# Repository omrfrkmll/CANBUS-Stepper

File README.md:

# ⚡ CANBUS-Stepper

<p align="center">
  <b>ESP32-S3 Based Closed-Loop Smart CAN Bus Stepper Motor Driver Board (v1.1)</b>
</p>

<p align="center">

</p>

<p align="center">
  <a href="#-overview">Overview</a> •
  <a href="#-development-status">Development Status</a> •
  <a href="#-hardware-features--specifications">Hardware Specs</a> •
  <a href="#-pcb--hardware-preview">PCB Preview</a> •
  <a href="#-schematics--mechanical-cad">Schematic & CAD</a> •
  <a href="#-firmware--control-sdk">Firmware & SDK</a> •
  <a href="#-official-hardware--custom-engineering">Official Hardware & Services</a> •
  <a href="#-license">License</a>
</p>

---

## 📌 Overview

**CANBUS-Stepper** is a high-performance smart stepper motor driver board powered by the **ESP32-S3** dual-core microcontroller. Designed specifically for 3D printer toolheads, robotic actuators, AGVs, CNC axes, and industrial automation, this board integrates:

- **Ultra-Quiet Motor Drive**: Trinamic TMC2209-LA driver with StealthChop2™, SpreadCycle™, and StallGuard4™ sensorless homing.
- **Closed-Loop Position Feedback**: High-precision AS5600 12-bit magnetic rotary encoder mounted coaxially on the bottom layer to eliminate missed steps.
- **Native CAN Bus Communication**: Automotive-grade TI TCAN3413 transceiver supporting high-speed CAN and CAN FD logic with 3.3V logic.
- **Industrial Wide-Input Power**: High-efficiency TI LMR33630 36V / 3A synchronous step-down DC-DC buck regulator + ultra-low-noise 3.3V LDO.
- **Multi-Stage Protection Circuits**: Reverse polarity P-MOSFET, transient voltage suppressors (TVS), ESD diode arrays, and resettable PPTC fuses.
- **Compact NEMA 17 Footprint**: Fits directly onto the rear face of standard 42mm x 42mm NEMA 17 stepper motors (40.3mm x 40.3mm profile with corner chamfers and M3 mounting holes).

---

## 🚧 Development Status

| Component | Status | Details |
| :--- | :---: | :--- |
| **Schematic Design** | ✅ Complete | Hierarchical schematic design, [PDF export available](docs/schematics/CANBUS_Stepper_v1.1_Schematic.pdf) |
| **PCB Layout (v1.1)** | ✅ Complete | 2-Layer 1.6mm FR4, DRC clean, planar ESP32-S3 pin routing |
| **Component Mapping (BOM)** | ✅ Complete | 43 unique lines / 67 components 100% mapped with LCSC part numbers |
| **3D CAD STEP Models** | ✅ Complete | Exported 3D assembly ([`step/canbus-stepper-v1.1.step`](step/canbus-stepper-v1.1.step)) ready for enclosure design |
| **Physical Prototyping** | 🔄 In Progress | Prototype PCBA fabrication & physical hardware bring-up |
| **Firmware & Control SDK** | 🔄 In Progress | ESP32-S3 TWAI CAN driver, closed-loop PID loop & Klipper node support |

---

## 🛠️ Hardware Features & Specifications

### 🧠 Core System & Processing
- **MCU**: **ESP32-S3-MINI-1-N4R2** (Dual-core Xtensa® 32-bit LX7 @ 240 MHz, 2.4 GHz Wi-Fi 4 + Bluetooth 5 LE, 4 MB Flash, 2 MB Quad SPI PSRAM).
- **USB Interface**: Native Full-Speed USB 2.0 via Type-C connector with hardware CDC serial console & JTAG debugging support.

### ⚡ Motor Drive & Closed-Loop Regulation
- **Stepper Driver**: **Trinamic TMC2209-LA** (VQFN-28 package with thermal vias).
  - Operating Voltage: Up to 28V DC (recommended 12V – 24V).
  - Current Capability: 2.0A RMS (2.8A Peak) motor phase current.
  - Features: StealthChop2™ (silent operation), SpreadCycle™ (high dynamic torque), StallGuard4™ (load measurement & sensorless homing), CoolStep™ (energy saving).
  - Interface: UART control for dynamic microstepping configuration (up to 256 microsteps) and real-time current scaling.
- **Position Sensor**: **AMS AS5600-ASOT** 12-Bit On-Axis Magnetic Rotary Encoder.
  - Position Resolution: 4096 steps/rev (0.087° resolution).
  - Mounting: Centered directly on PCB bottom layer for coaxial alignment with motor shaft diametral magnet.
  - Interface: Fast-mode I2C (400 kHz).

### 🌐 Bus Communication & Power Regulation
- **CAN Bus Transceiver**: **TI TCAN3413DRBR** 3.3V CAN FD Transceiver with 3.3V V_IO logic interface and ±58V bus fault protection.
- **Main DC-DC Buck Converter**: **TI LMR33630CRNXR** Synchronous Step-Down Regulator (3.8V – 36V input range, 3.0A continuous output @ 2.1 MHz switching frequency) with **Changjiang FNR4020S4R7MT** (4.7µH / 2A) shielded power inductor.
- **MCU & Analog LDO**: **TI TLV75533PDRVR** 500mA ultra-low-dropout 3.3V regulator providing clean power to ESP32-S3 and sensors.
- **Bulk Filtering**: 100µF / 35V Low-ESR aluminum electrolytic bulk capacitor (6.3mm x 5.8mm SMD) for motor switching current ripple suppression.

### 🛡️ Protection & Safety Architecture
- **Reverse Polarity Protection**: **AON7403** (-30V / -50A, 8.5mΩ R_DS(on) P-Channel MOSFET) with Zener gate clamping.
- **Overcurrent Protection**:
  - 1.5A / 24V Resettable PPTC fuse (`1210L150/24WR`) on main 24V DC input rail.
  - 500mA / 16V Resettable PPTC fuse (`SMDH0805B050TF`) on USB VBUS power line.
- **Transient & ESD Protection**:
  - **PESD1CAN** TVS diode array on CAN Bus differential lines (CAN_H / CAN_L).
  - **SMAJ28A** 28V / 400W Transient Voltage Suppressor on main 24V DC input.
  - **STMicroelectronics USBLC6-2P6** ultra-low capacitance ESD protection array on USB D+/D- lines.
  - **MBR0520** Schottky diode for safe USB/Main power OR-ing.

### 🔌 Connectors, Ports & Controls
| Connector / Component | Type / Footprint | Function |
| :--- | :--- | :--- |
| **USB-C** | 16-Pin USB Type-C Receptacle | Firmware flashing, USB CDC serial debugging & power |
| **24V Power In / Out** | 2x Molex Micro-Fit 3.0 (436500209) 2-Pin | 24V Main power input & daisy-chain pass-through |
| **Motor Output** | JST PH 4-Pin SMD (S4B-PH-SM4-K-TB) | 4-wire bipolar stepper motor phases (A1, A2, B1, B2) |
| **Qwiic / I2C Port** | JST SH 4-Pin (1.0mm) Horizontal | External I2C sensors, OLED displays & expansions (3.3V, GND, SDA, SCL) |
| **AUX Port** | JST SH 4-Pin (1.0mm) Horizontal | Auxiliary GPIOs for endstops, bed probes, or toolhead sensors |
| **CAN Bus In / Out** | 2x JST SH 2-Pin (SM02B-SRSS-TB) | CAN Bus differential input & daisy-chain pass-through (CAN_H, CAN_L) |
| **OLED Display FPC** | Amphenol SFV30R-2STBE1HLF (30-Pin 0.5mm) | Bare COG OLED display panel interface (SSD1306) |
| **CAN Termination** | SMD Slide Switch (`MSK12C01G15-W`) | Switchable 120Ω CAN bus termination resistor |
| **Buttons & Indicators** | 2x Tactile Push-Buttons + 3x LEDs | RESET, BOOT/User buttons; Power, Driver, and CAN Status LEDs |

---

## 🖼️ PCB & Hardware Preview

<p align="center">
  
  &nbsp;&nbsp;
  
  <br>
  <i>Figure 1: CANBUS-Stepper v1.1 Component Layout — Top Layer (Left) & Bottom Layer (Right)</i>
</p>

---

## 📄 Schematics & Mechanical CAD

To enable seamless third-party software integration, driver development, and custom enclosure modeling, official hardware reference documents are provided:

1. **Schematic Circuit Diagrams (PDF)**:
   - Complete multi-sheet reference schematics are available in [`docs/schematics/CANBUS_Stepper_v1.1_Schematic.pdf`](docs/schematics/CANBUS_Stepper_v1.1_Schematic.pdf) (Legacy v1.0 available in [`docs/schematics/`](docs/schematics/)).
   - Details MCU pinouts, TMC2209 UART buses, CAN transceiver wiring, protection circuits, and sensor connectors.
2. **3D Mechanical STEP Assembly**:
   - Ready-to-import 3D CAD model: [`step/canbus-stepper-v1.1.step`](step/canbus-stepper-v1.1.step).
   - Accurate component heights, connector positions, and NEMA 17 rear mounting hole spacing (31.0mm x 31.0mm diagonal M3 holes).

---

## 📁 Repository Structure

```
CANBUS-Stepper/
├── README.md                      # Main project documentation & specifications
├── LICENSE                        # CC BY-NC-SA 4.0 (Hardware Reference) & MIT (Software)
├── .gitignore                     # Git ignore rules
├── docs/
│   ├── assets/                    # 3D PCB renders, board photos, and diagrams
│   └── schematics/                # Full PDF Schematic & Pinout reference documentation
│       ├── README.md              # Sheet breakdown and integration guide
│       └── CANBUS_Stepper_v1.1_Schematic.pdf
├── firmware/                      # ESP32-S3 Firmware, Protocol & SDK
│   ├── include/                   # Drivers, control loops, and headers
│   ├── src/                       # Motion controller, TWAI CAN, AS5600, TMC2209
│   ├── klipper/                   # Klipper toolhead configuration & docs
│   ├── platformio.ini             # PlatformIO build configuration
│   └── README.md                  # Firmware architecture & roadmap
└── step/                          # 3D CAD STEP Files for mechanical integration
    ├── canbus-stepper-v1.1.step   # Full 3D PCB assembly STEP model (v1.1)
    └── README.md                  # Mounting specifications & CAD guide
```

---

## 🧠 Firmware & Control SDK

The ESP32-S3 microcontroller firmware is developed under `firmware/` and targets both standalone robotic motion control and 3D printing ecosystems:

- **TWAI CAN Protocol**: High-speed command parser for position target streaming, velocity profiling, and status telemetry.
- **Closed-Loop PID Loop**: High-frequency reading from the AS5600 magnetic encoder with real-time step error correction and missed step prevention.
- **Klipper CAN Toolhead Support**: Compatibility with Klipper firmware for plug-and-play toolhead CAN node integration.
- **ROS2 & Micro-ROS**: Direct actuator node integration for robotic arms, wheeled rovers, and multi-axis mechanisms.
- **Open SDK**: Python and C++ driver libraries for controlling motors over USB-to-CAN adapters.

---

## 🛒 Official Hardware, Kits & Custom Engineering

Ensure guaranteed hardware quality and support ongoing development through **Official Pre-Assembled Hardware & Engineering Services**:

### 📦 Official Plug-and-Play Kits
- 🛠️ **Factory-Tested Boards**: 100% SMT assembled, flashed with factory test firmware, and validated under motor load.
- 🧲 **Complete Motor Kits**: Bundled with high-temperature NEMA 17 stepper motors, matched diametrically magnetized shaft magnets, 3D printed mounting brackets, and pre-crimped Molex/JST wire harnesses.
- ☕ **Support Ongoing Development**: Official hardware sales directly fund continuous firmware development, Klipper modules, and future hardware revisions.

### 🏢 B2B Custom Robotics & Turnkey Engineering
Need customized hardware or industrial integration for your commercial robotics or automation project?
- **Custom PCB Redesigns** (Multi-axis drivers, 48V high-voltage input, RS485 / EtherCAT / DroneCAN).
- **Industrial Firmware & ROS2 / Micro-ROS Drivers**.
- **Volume Batch Manufacturing & PCBA Sourcing**.

👉 *For pre-orders, volume batch requests, or custom engineering consulting, please reach out via GitHub Issues or contact the maintainer.*

---

## 📜 License

This project follows a **Hybrid Open-Software & Reference-Hardware** model:

- 🛡️ **Hardware Reference (Schematics, Pinouts, Mechanical Specs & 3D STEP)**: [Creative Commons Attribution-NonCommercial-ShareAlike 4.0 International (CC BY-NC-SA 4.0)](https://creativecommons.org/licenses/by-nc-sa/4.0/).
- 💻 **Firmware & Software Stack**: [MIT License](LICENSE).
- 🏷️ **Trademarks & Official Branding**: The "CANBUS-Stepper" and "ILTERAY" names and logos represent official tested hardware.

---

<p align="center">
  <b>CANBUS-Stepper</b> • Open-Source Smart Motion Control
</p>

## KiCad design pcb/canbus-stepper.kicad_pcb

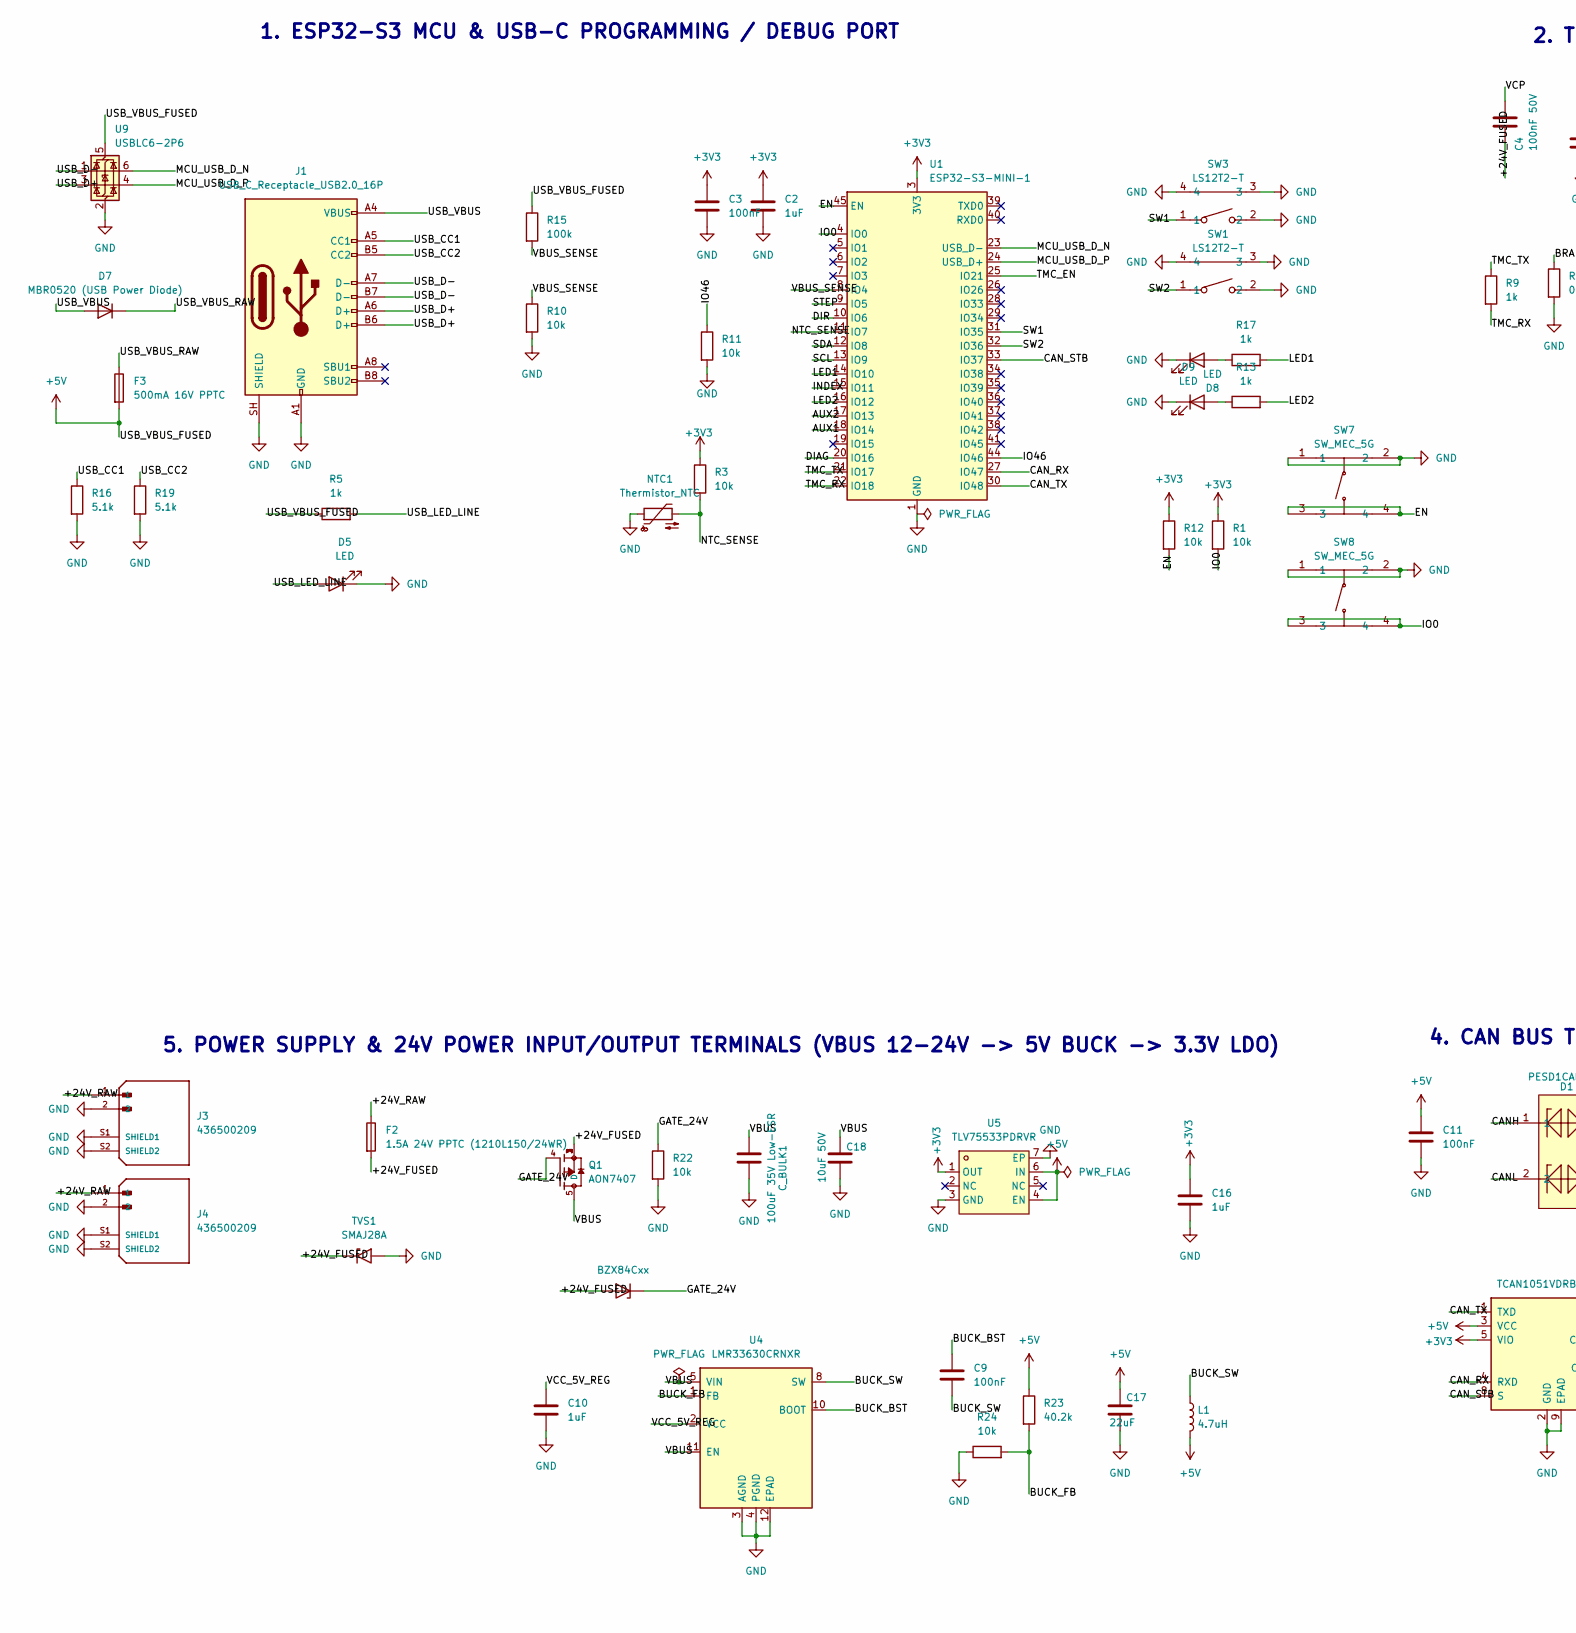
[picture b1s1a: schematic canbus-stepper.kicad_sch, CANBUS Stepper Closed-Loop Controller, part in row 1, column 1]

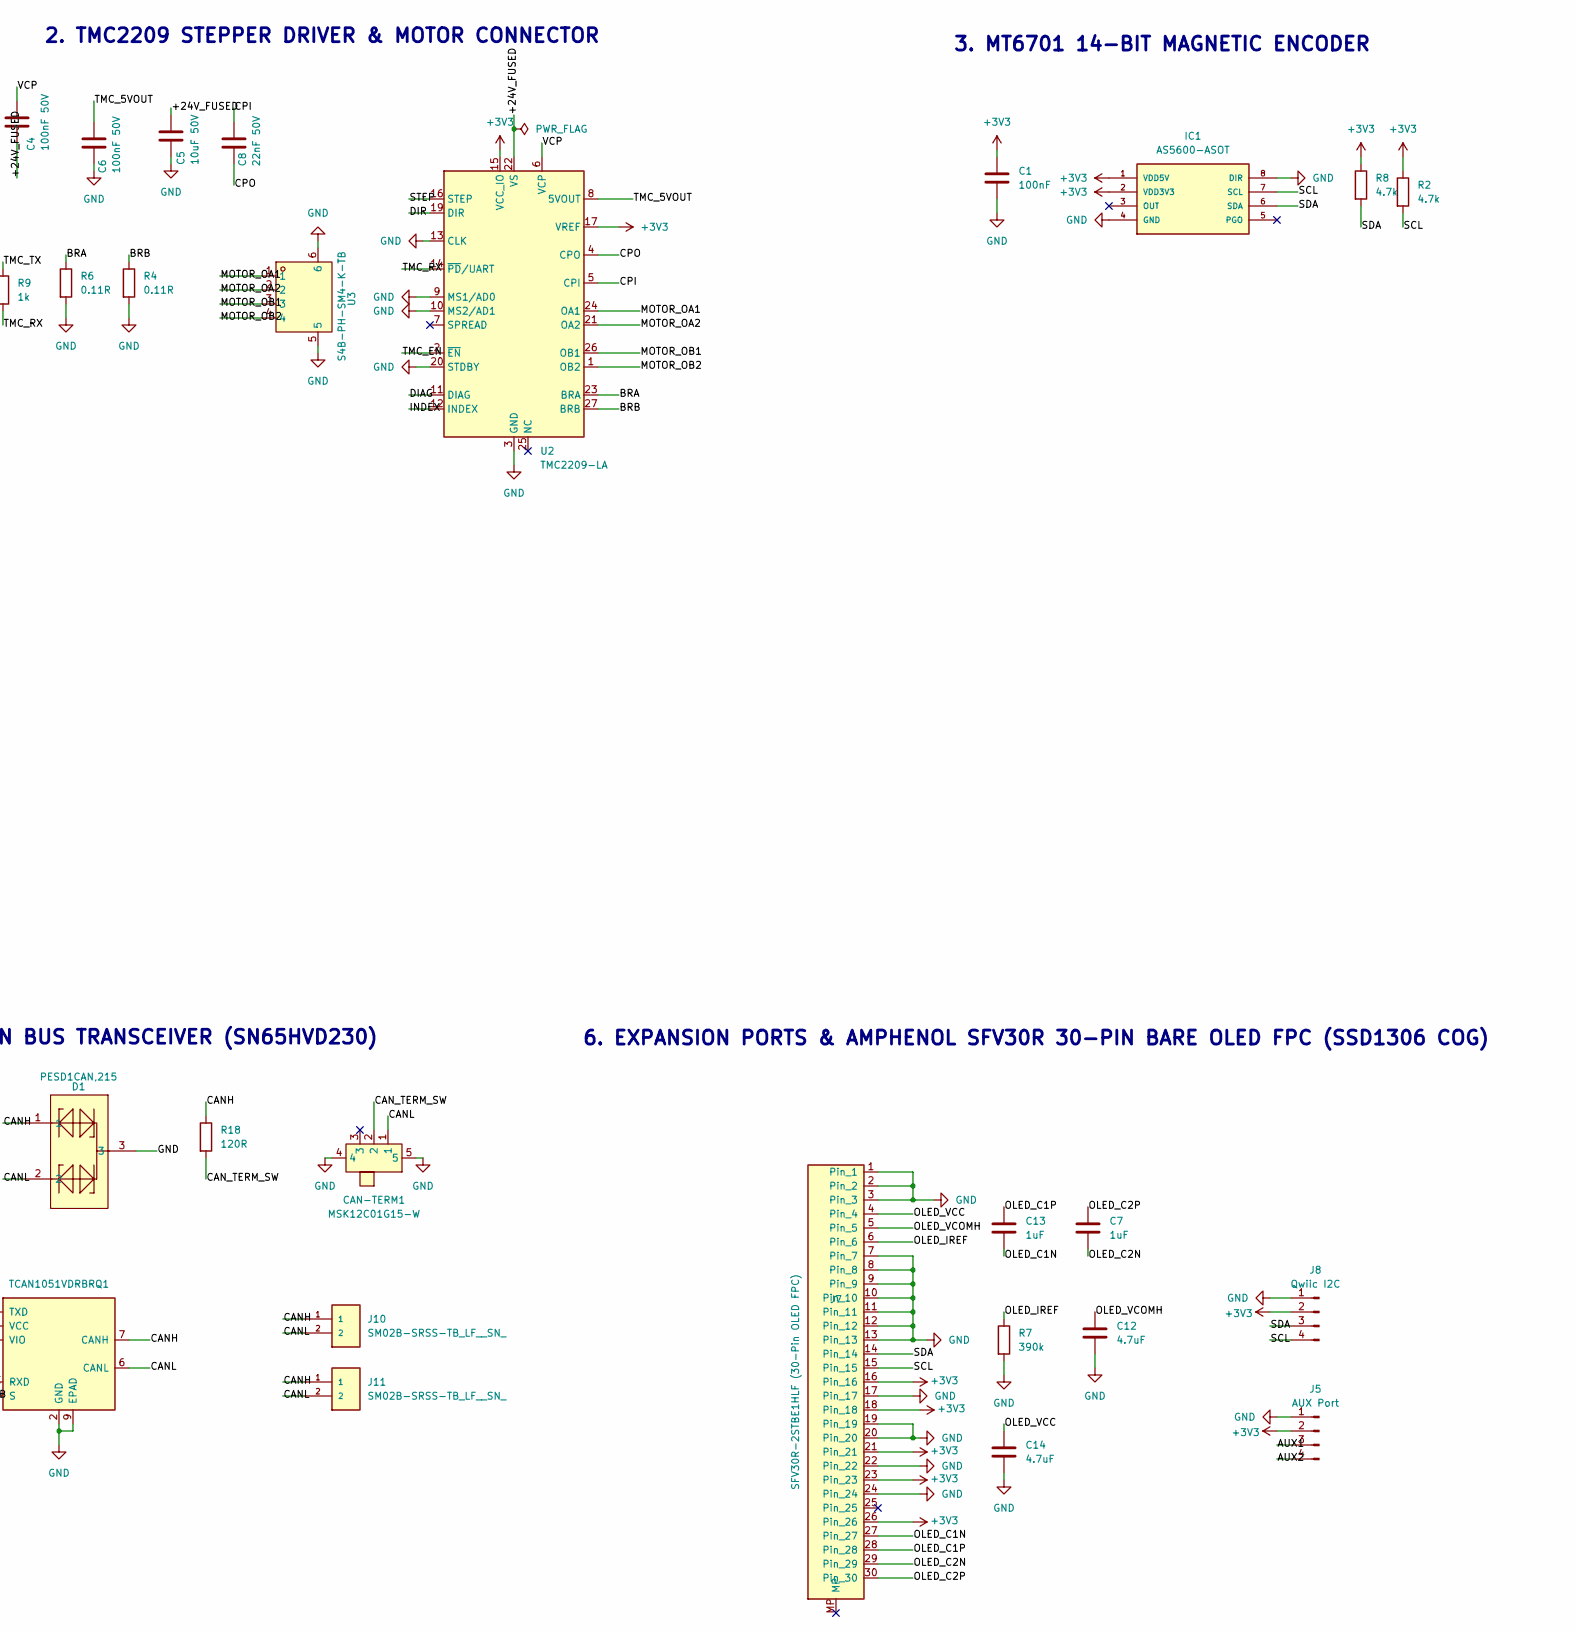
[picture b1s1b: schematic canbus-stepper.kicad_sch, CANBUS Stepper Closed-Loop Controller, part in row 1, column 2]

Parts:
C1, C3, C9, C11: 100nF; C_0402_1005Metric; DigikeyPN GCM155R71H104KE02J
C2, C10, C16: 1uF; C_0402_1005Metric; DigikeyPN JMK105BJ105KV-F
C4, C6: 100nF 50V; C_0402_1005Metric; DigikeyPN GRM155R71H104KE14J
C5, C18: 10uF 50V; C_1206_3216Metric; DigikeyPN 885012108022
C7, C13: 1uF; C_0402_1005Metric; DigikeyPN 478-KGM05AR50J105KHCT-ND
C8: 22nF 50V; C_0402_1005Metric; DigikeyPN GRM155R71H223KA12D
C12, C14: 4.7uF; C_0402_1005Metric; LCSC Part C23733
C17: 22uF; C_0805_2012Metric; DigikeyPN CL21A226KPCLRNC
CAN-TERM1: MSK12C01G15-W; SW-SMD_MSK12C01G15-W; MPN MSK12C01G15-W; LCSC Part C22435664
C_BULK1: 100uF 35V Low-ESR; C_Elec_6.3x5.8; DigikeyPN EEH-ZK1V101XP
D1: PESD1CAN,215; SOT-23_L2.9-W1.3-P1.90-LS2.4-BR; MPN PESD1CAN,215; LCSC Part C15771
D5, D8, D9: LED; LED_0805_2012Metric; DigikeyPN LTST-C171GKT,LTST-C171KRKT
D6: BZX84Cxx; SOT-23; DigikeyPN BZX84C12LT1G
D7: MBR0520 (USB Power Diode); D_SOD-323; DigikeyPN MBR0520L
F2: 1.5A 24V PPTC (1210L150/24WR); Fuse_1210_3225Metric; DigikeyPN 2920L330/24MR
F3: 500mA 16V PPTC; Fuse_0805_2012Metric; DigikeyPN SMDH0805B050TF
IC1: AS5600-ASOT; MOUSER_PART_NUMBER 985-AS5600-ASOT
J1: USB_C_Receptacle_USB2.0_16P; USB_C_Receptacle_16P; DigikeyPN UJ20-C-H-G-SMT-4-P16-TR
J3, J4: 436500209; MOLEX_436500209; PARTREV E2; DigikeyPN 0436500209
J5: AUX Port; JST_SH_SM04B-SRSS-TB_1x04-1MP_P1.00mm_Horizontal; DigikeyPN SM02B-SRSS-TB
J7: SFV30R-2STBE1HLF (30-Pin OLED FPC); AMPHENOL_SFV30R-2STBE1HLF; DigikeyPN SFV30R-2STBE1HLF
J8: Qwiic I2C; JST_SH_SM04B-SRSS-TB_1x04-1MP_P1.00mm_Horizontal; DigikeyPN SM02B-SRSS-TB
J10, J11: SM02B-SRSS-TB_LF__SN_; DigikeyPN SM02B-SRSS-TB
L1: 4.7uH; L_0603_1608Metric; DigikeyPN MLZ1608M4R7WT000
NTC1: Thermistor_NTC; R_0603_1608Metric; DigikeyPN NCU18WF104E60RB
Q1: AON7407; PARTREV 0; DigikeyPN AON7407
R1, R3, R10, R11, R12, R22, R24: 10k; R_0402_1005Metric; DigikeyPN CRGCQ0402J10K
R2, R8: 4.7k; R_0402_1005Metric; DigikeyPN RC0402FR-074K7L
R4, R6: 0.11R; R_1206_3216Metric; DigikeyPN ERJ-8BSFR11V
R5, R9, R13, R17: 1k; R_0402_1005Metric; DigikeyPN RC0402JR-071KL
R7: 390k; R_0402_1005Metric; LCSC Part C25557
R15: 100k; R_0402_1005Metric; DigikeyPN CRGCQ0402J100K
R16, R19: 5.1k; R_0402_1005Metric; DigikeyPN RC0402FR-075K1L
R18: 120R; R_0402_1005Metric; DigikeyPN RC0402JR-07120RL
R23: 40.2k; R_0402_1005Metric; DigikeyPN RC0402FR-0740K2L
SW1, SW3: LS12T2-T; SW-SMD_2P-TS24CA; MPN TS24CA; LCSC Part C393942
SW7, SW8: SW_MEC_5G; SW-SMD_4P-L4.2-W3.4-P2.15-LS5.2; MPN TS3425PA 250gf; DigikeyPN TL3365AF180QG
TVS1: SMAJ28A; D_SMA; DigikeyPN SMAJ28A
U1: ESP32-S3-MINI-1; ESP32-S2-MINI-1; DigikeyPN ESP32-S3-MINI-1-N4R2
U2: TMC2209-LA; VQFN-28-1EP_5x5mm_P0.5mm_EP3.7x3.7mm_ThermalVias; DigikeyPN TMC2209-LA-T
U3: S4B-PH-SM4-K-TB; CONN-SMD_S4B-PH-SM4-K-TB-LF-SN; MPN S4B-PH-SM4-K-TB(LF)(SN); LCSC Part C265332
U4: LMR33630CRNXR; DigikeyPN LMR33630CRNXR
U5: TLV75533PDRVR; WSON-6_L2.0-W2.0-P0.65-TL-EP; MPN TLV75533PDRVR; LCSC Part C2861750
U6: TCAN1051VDRBRQ1; DigikeyPN TCAN1051VDRBRQ1
U9: USBLC6-2P6; SOT-666; DigikeyPN USBLC6-2SC6_UMW

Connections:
+3V3: C1.1, C2.1, C3.1, C16.1, IC1.1 (VDD5V), IC1.2 (VDD3V3), J5.2, J7.16, J7.18, J7.21, J7.23, J7.26, J8.2, R1.1, R2.1, R3.1, R8.1, R12.1, U1.3 (3V3), U2.15 (VCC_IO), U2.17 (VREF), U5.1 (OUT), U6.5 (VIO)
+5V: C11.1, C17.1, F3.2, L1.2, R5.1, R15.1, R23.1, U5.4 (EN), U5.6 (IN), U6.3 (VCC), U9.5 (VBUS)
/+24V_FUSED: C4.2, C5.1, D6.1 (A), F2.2, Q1.1, Q1.2, Q1.3, TVS1.1 (A1), U2.22 (VS), U2.28 (VS)
/+24V_RAW: F2.1, J3.1, J4.1
/AUX1: J5.3, U1.18 (IO14)
/AUX2: J5.4, U1.17 (IO13)
/BRA: R6.1, U2.23 (BRA)
/BRB: R4.1, U2.27 (BRB)
/BUCK_BST: C9.1, U4.10 (BOOT)
/BUCK_FB: R23.2, R24.2, U4.1 (FB)
/BUCK_SW: C9.2, L1.1, U4.8 (SW), U4.9 (SW)
/CANH: D1.1, J10.1, J11.1, R18.1, U6.7 (CANH)
/CANL: CAN-TERM1.1, D1.2, J10.2, J11.2, U6.6 (CANL)
/CAN_RX: U1.27 (IO47), U6.4 (RXD)
/CAN_STB: U1.33 (IO37), U6.8 (S)
/CAN_TERM_SW: CAN-TERM1.2, R18.2
/CAN_TX: U1.30 (IO48), U6.1 (TXD)
/CPI: C8.1, U2.5 (CPI)
/CPO: C8.2, U2.4 (CPO)
/DIAG: U1.20 (IO16), U2.11 (DIAG)
/DIR: U1.10 (IO6), U2.19 (DIR)
/EN: R12.2, SW7.3, SW7.4, U1.45 (EN)
/GATE_24V: D6.3 (K), Q1.4, R22.1
/INDEX: U1.15 (IO11), U2.12 (INDEX)
/IO0: R1.2, SW8.3, SW8.4, U1.4 (IO0)
/IO46: R11.1, U1.44 (IO46)
/LED1: R17.2, U1.14 (IO10)
/LED2: R13.2, U1.16 (IO12)
/MCU_USB_D_N: U1.23 (USB_D-), U9.6 (I/O1)
/MCU_USB_D_P: U1.24 (USB_D+), U9.4 (I/O2)
/MOTOR_OA1: U2.24 (OA1), U3.1
/MOTOR_OA2: U2.21 (OA2), U3.2
/MOTOR_OB1: U2.26 (OB1), U3.3
/MOTOR_OB2: U2.1 (OB2), U3.4
/NTC_SENSE: NTC1.2, R3.2, U1.11 (IO7)
/SCL: IC1.7 (SCL), J7.15, J8.4, R2.2, U1.13 (IO9)
/SDA: IC1.6 (SDA), J7.14, J8.3, R8.2, U1.12 (IO8)
/STEP: U1.9 (IO5), U2.16 (STEP)
/SW1: SW3.1, U1.31 (IO35)
/SW2: SW1.1, U1.32 (IO36)
/TMC_5VOUT: C6.1, U2.8 (5VOUT)
/TMC_EN: U1.25 (IO21), U2.2 (~EN)
/TMC_RX: R9.2, U1.22 (IO18), U2.14 (~PD/UART)
/TMC_TX: R9.1, U1.21 (IO17)
/USB_CC1: J1.A5 (CC1), R16.1
/USB_CC2: J1.B5 (CC2), R19.1
/USB_D+: J1.A6 (D+), J1.B6 (D+), U9.3 (I/O2)
/USB_D-: J1.A7 (D-), J1.B7 (D-), U9.1 (I/O1)
/USB_LED_LINE: D5.2 (A), R5.2
/USB_VBUS: D7.2 (A), J1.A4 (VBUS), J1.A9 (VBUS), J1.B4 (VBUS), J1.B9 (VBUS)
/USB_VBUS_RAW: D7.1 (K), F3.1
/VBUS_SENSE: R10.1, R15.2, U1.8 (IO4)
/VCC_5V_REG: C10.1, U4.2 (VCC)
/VCP: C4.1, U2.6 (VCP)
GND: C1.2, C2.2, C3.2, C5.2, C6.2, C10.2, C11.2, C12.2, C14.2, C16.2, C17.2, C18.2, CAN-TERM1.4, CAN-TERM1.5, C_BULK1.2, D1.3, D5.1 (K), D8.1 (K), D9.1 (K), IC1.4 (GND), IC1.8 (DIR), J1.A1 (GND), J1.A12 (GND), J1.B1 (GND), J1.B12 (GND), J1.SH (SHIELD), J3.2, J3.S1 (SHIELD1), J3.S2 (SHIELD2), J4.2, J4.S1 (SHIELD1), J4.S2 (SHIELD2), J5.1, J7.1, J7.2, J7.3, J7.7, J7.8, J7.9, J7.10, J7.11, J7.12, J7.13, J7.17, J7.19, J7.20, J7.22, J7.24, J8.1, NTC1.1, R4.2, R6.2, R7.2, R10.2, R11.2, R16.2, R19.2, R22.2, R24.1, SW1.2, SW1.3, SW1.4, SW3.2, SW3.3, SW3.4, SW7.1, SW7.2, SW8.1, SW8.2, TVS1.2 (A2), U1.1 (GND), U1.2 (GND), U1.42 (GND), U1.43 (GND), U1.46 (GND), U1.47 (GND), U1.48 (GND), U1.49 (GND), U1.50 (GND), U1.51 (GND), U1.52 (GND), U1.53 (GND), U1.54 (GND), U1.55 (GND), U1.56 (GND), U1.57 (GND), U1.58 (GND), U1.59 (GND), U1.60 (GND), U1.61 (GND), U1.62 (GND), U1.63 (GND), U1.64 (GND), U1.65 (GND), U2.3 (GND), U2.9 (MS1/AD0), U2.10 (MS2/AD1), U2.13 (CLK), U2.18 (GND), U2.20 (STDBY), U2.29 (GND), U3.5, U3.6, U4.3 (AGND), U4.4 (PGND), U4.12 (EPAD), U5.3 (GND), U5.7 (EP), U6.2 (GND), U6.9 (EPAD), U9.2 (GND); also elsewhere on the board
unnamed: C7.1, J7.30
unnamed: C7.2, J7.29
unnamed: C12.1, J7.5
unnamed: C13.1, J7.28
unnamed: C13.2, J7.27
unnamed: C14.1, J7.4
unnamed: D8.2 (A), R17.1
unnamed: D9.2 (A), R13.1
unnamed: J7.6, R7.1
VIN: C18.1, C_BULK1.1, Q1.5 (D), Q1.6 (D), Q1.7 (D), Q1.8 (D), U4.5 (VIN), U4.6 (VIN), U4.7 (VIN), U4.11 (EN)

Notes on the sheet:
2. TMC2209 STEPPER DRIVER & MOTOR CONNECTOR
5. POWER SUPPLY & 24V POWER INPUT/OUTPUT TERMINALS (VBUS 12-24V -> 5V BUCK -> 3.3V LDO)
6. EXPANSION PORTS & AMPHENOL SFV30R 30-PIN BARE OLED FPC (SSD1306 COG)
1. ESP32-S3 MCU & USB-C PROGRAMMING / DEBUG PORT
4. CAN BUS TRANSCEIVER (SN65HVD230)
3. MT6701 14-BIT MAGNETIC ENCODER

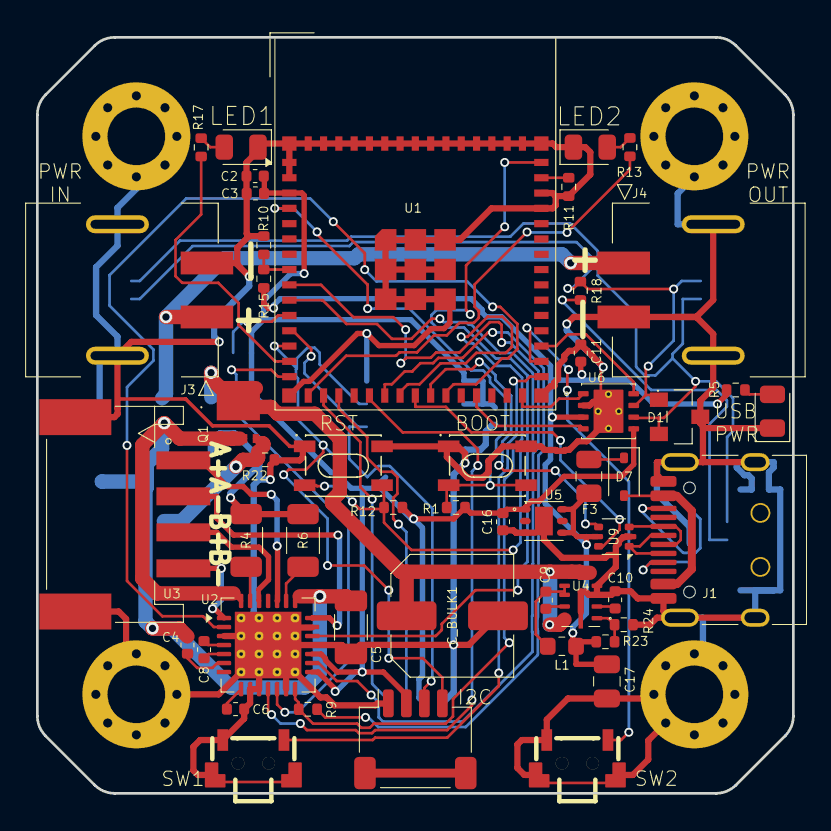
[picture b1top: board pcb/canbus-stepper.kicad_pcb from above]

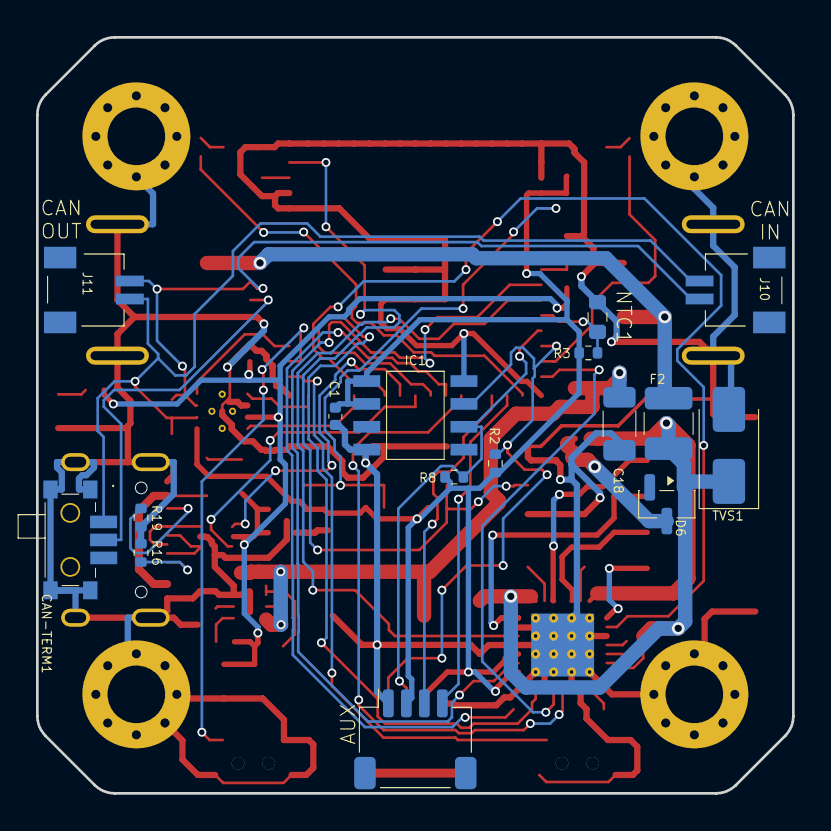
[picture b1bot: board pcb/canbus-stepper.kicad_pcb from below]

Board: 2 copper layers, 42.0 x 42.0 mm, 67 parts (16 on the bottom side), 58 nets.

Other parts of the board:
BOARD1: NEMA17_PCB_Outline; NEMA17_PCB_Outline_42.0x42.0_8Fillets

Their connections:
GND: BOARD1.H1, BOARD1.H1_V1, BOARD1.H1_V2, BOARD1.H1_V3, BOARD1.H1_V4, BOARD1.H1_V5, BOARD1.H1_V6, BOARD1.H1_V7, BOARD1.H1_V8, BOARD1.H2, BOARD1.H2_V1, BOARD1.H2_V2, BOARD1.H2_V3, BOARD1.H2_V4, BOARD1.H2_V5, BOARD1.H2_V6, BOARD1.H2_V7, BOARD1.H2_V8, BOARD1.H3, BOARD1.H3_V1, BOARD1.H3_V2, BOARD1.H3_V3, BOARD1.H3_V4, BOARD1.H3_V5, BOARD1.H3_V6, BOARD1.H3_V7, BOARD1.H3_V8, BOARD1.H4, BOARD1.H4_V1, BOARD1.H4_V2, BOARD1.H4_V3, BOARD1.H4_V4, BOARD1.H4_V5, BOARD1.H4_V6, BOARD1.H4_V7, BOARD1.H4_V8; also elsewhere on the board

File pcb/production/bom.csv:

Designator,Footprint,Quantity,Value,LCSC Part #
"C1, C11, C3, C9",0402,4,100nF,C76698
"C10, C16, C2",0402,3,1uF,C29266
C17,0805,1,22uF,C1532
"C18, C5",1206,2,10uF 50V,C13585
"C4, C6",0402,2,100nF 50V,C1581
C8,0402,1,22nF 50V,C1532
CAN-TERM1,SW-SMD_MSK12C01G15-W,1,MSK12C01G15-W,C22435664
C_BULK1,C_Elec_6.3x5.8,1,100uF 35V Low-ESR,C128464
D1,SOT-23_L2.9-W1.3-P1.90-LS2.4-BR,1,"PESD1CAN,215",C15771
"D5, D8, D9",0805,3,LED,C2295
D6,SOT-23,1,BZX84Cxx,C12773
D7,D_SOD-323,1,MBR0520 (USB Power Diode),C23848
F2,1210,1,1.5A 24V PPTC (1210L150/24WR),C42376298
F3,0805,1,500mA 16V PPTC,C44606787
IC1,AS5600-ASOT,1,AS5600-ASOT,C499458
J1,USB_C_Receptacle_16P,1,USB_C_Receptacle_USB2.0_16P,C165948
"J10, J11",SM02B-SRSS-TB_LF__SN_,2,SM02B-SRSS-TB_LF__SN_,C160402
"J3, J4",MOLEX_436500209,2,436500209,C2995529
J5,JST_SH_SM04B-SRSS-TB_1x04-1MP_P1.00mm_Horizontal,1,AUX Port,C437064
J8,JST_SH_SM04B-SRSS-TB_1x04-1MP_P1.00mm_Horizontal,1,Qwiic I2C,C437064
L1,0603,1,4.7uH,C114862
NTC1,0603,1,Thermistor_NTC,C52205399
Q1,AON7407,1,AON7407,C176756
"R1, R10, R11, R12, R22, R24, R3",0402,7,10k,C100572
"R13, R17, R5, R9",0402,4,1k,C100571
R15,0402,1,100k,C100197
"R16, R19",0402,2,5.1k,C25905
R18,0402,1,120R,C100580
"R2, R8",0402,2,4.7k,C25940
R23,0402,1,40.2k,C11586
"R4, R6",1206,2,0.11R,C82532
"SW1, SW3",SW-SMD_2P-TS24CA,2,LS12T2-T,C393942
"SW7, SW8",SW-SMD_4P-L4.2-W3.4-P2.15-LS5.2,2,SW_MEC_5G,C668584
TVS1,D_SMA,1,SMAJ28A,C353458
U1,ESP32-S2-MINI-1,1,ESP32-S3-MINI-1,C3013941
U2,VQFN-28-1EP_5x5mm_P0.5mm_EP3.7x3.7mm_ThermalVias,1,TMC2209-LA,C2150710
U3,CONN-SMD_S4B-PH-SM4-K-TB-LF-SN,1,S4B-PH-SM4-K-TB,C265332
U4,LMR33630CRNXR,1,LMR33630CRNXR,C2071783
U5,WSON-6_L2.0-W2.0-P0.65-TL-EP,1,TLV75533PDRVR,C2861750
U6,TCAN1051VDRBRQ1,1,TCAN1051VDRBRQ1,C2671516
U9,SOT-666,1,USBLC6-2P6,C15999

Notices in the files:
README.md:
Hardware License
